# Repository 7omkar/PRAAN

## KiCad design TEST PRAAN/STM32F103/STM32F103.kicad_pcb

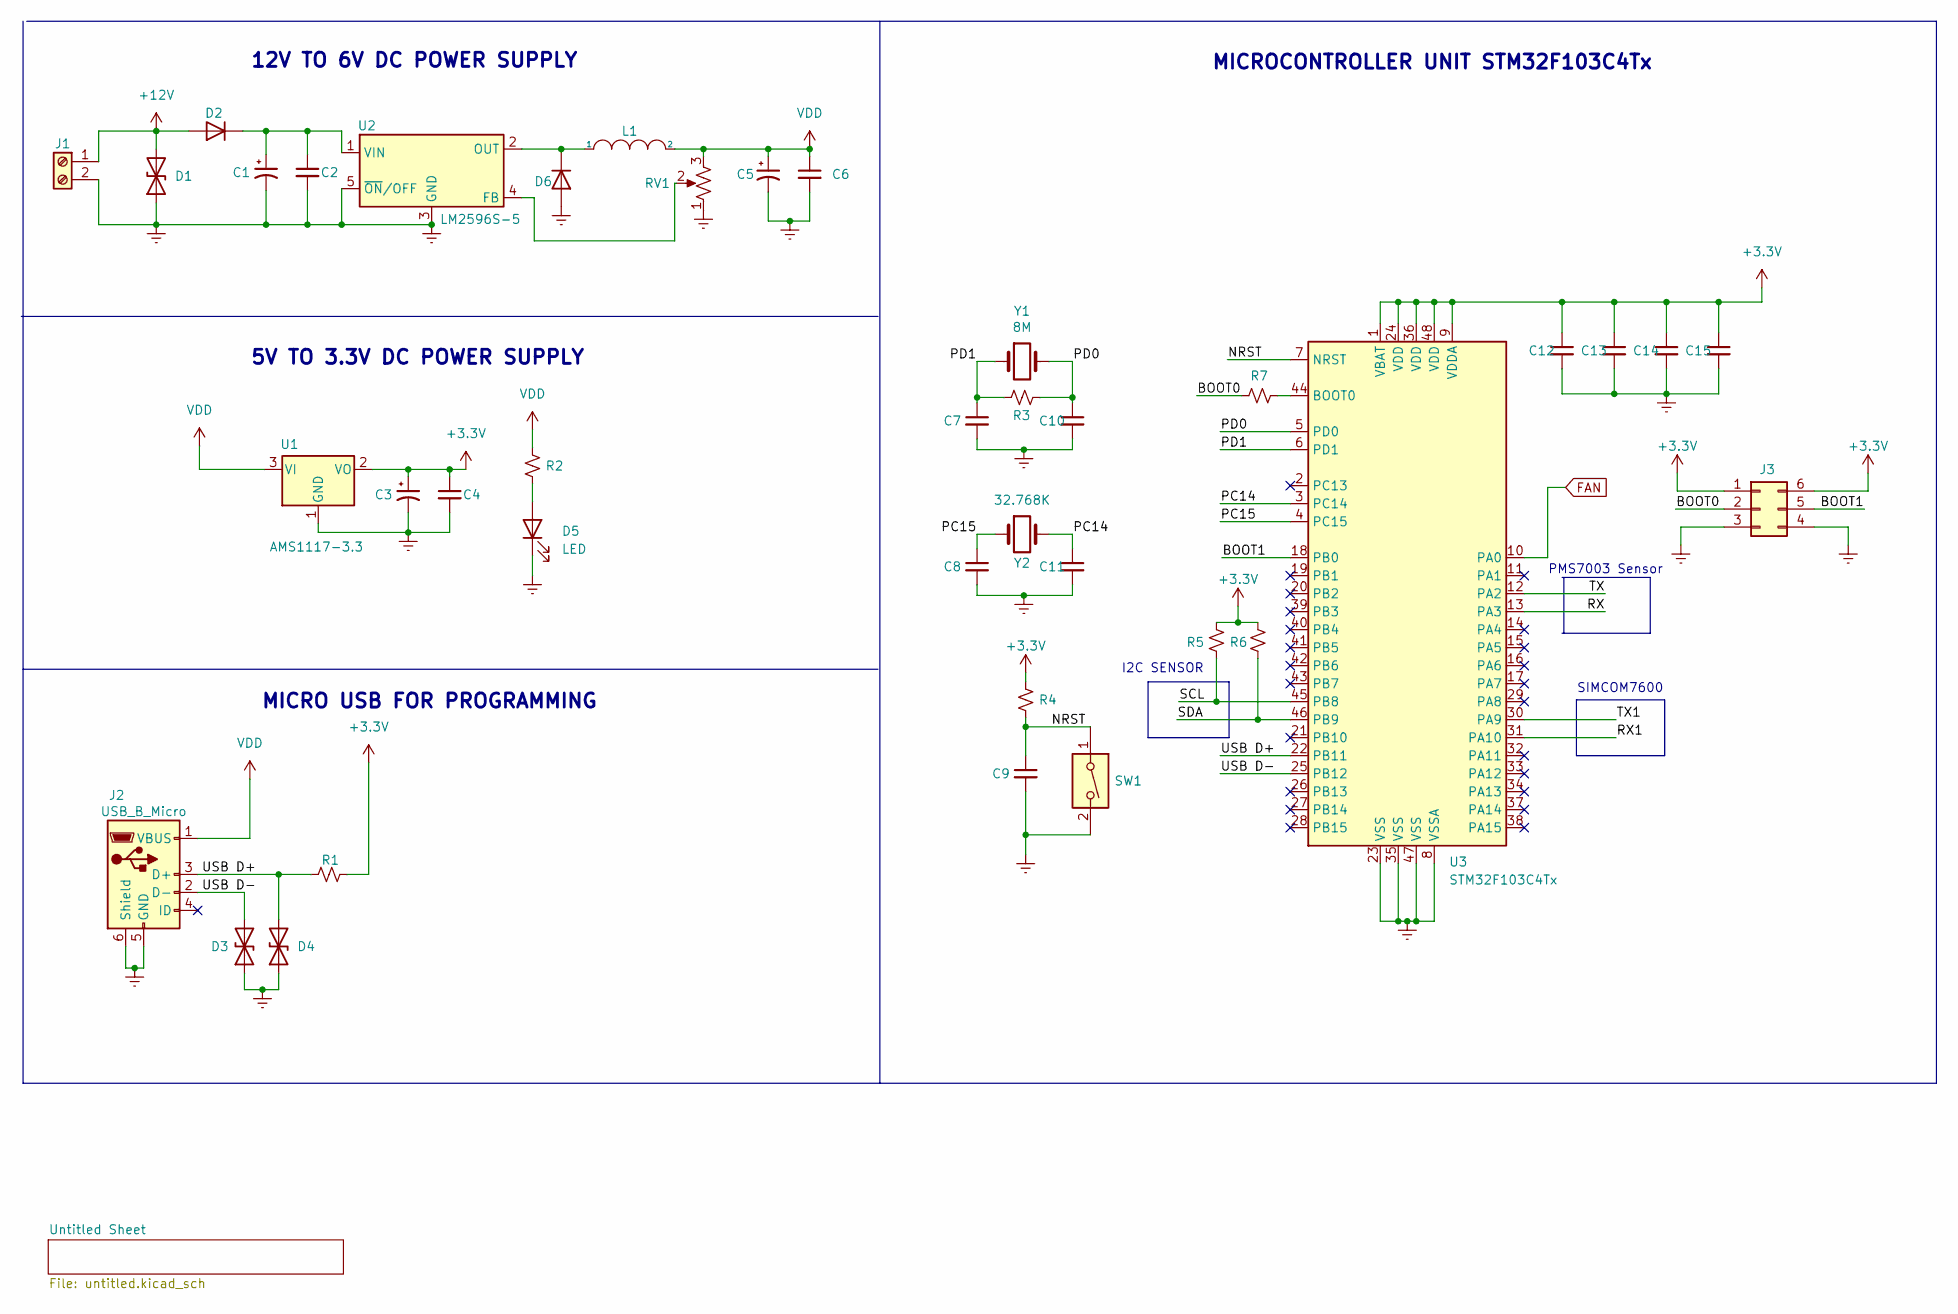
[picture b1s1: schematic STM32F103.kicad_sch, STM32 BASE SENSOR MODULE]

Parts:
C1, C3, C5: 470uf 25V; CP_Elec_5x5.8
C2, C4, C6, C12, C14: 0.1uf 50V; C_0805_2012Metric_Pad1.18x1.45mm_HandSolder
C7, C8, C9, C10, C11: 22pf 50V; C_0805_2012Metric_Pad1.18x1.45mm_HandSolder
C13, C15: 10uf 50V; C_0805_2012Metric_Pad1.18x1.45mm_HandSolder
D1, D3, D4: D_TVS; D_SOD-123
D2, D6: SS34; D_SMA
D5: LED; LED_0805_2012Metric_Pad1.15x1.40mm_HandSolder
J1: Screw_Terminal_01x02; TerminalBlock_Phoenix_MKDS-3-2-5.08_1x02_P5.08mm_Horizontal
J2: USB_B_Micro; USB_Micro-B_Molex-105017-0001
J3: Conn_02x03_Counter_Clockwise; PinHeader_2x03_P2.54mm_Vertical
L1: INDUCTOR; L_2512_6332Metric_Pad1.52x3.35mm_HandSolder
R1: 1.5K; R_0805_2012Metric_Pad1.20x1.40mm_HandSolder
R2, R4, R5, R6: 1K; R_0805_2012Metric_Pad1.20x1.40mm_HandSolder
R3: 10M; R_0805_2012Metric_Pad1.20x1.40mm_HandSolder
R7: 10K; R_0805_2012Metric_Pad1.20x1.40mm_HandSolder
RV1: 10K; Potentiometer_Bourns_3266W_Vertical
SW1: SW_DIP_x01; SW_PUSH_6mm_H5mm
U1: AMS1117-3.3; SOT-223-3_TabPin2
U2: LM2596S-5; TO-263-5_TabPin3
U3: STM32F103C4Tx; LQFP-48_7x7mm_P0.5mm
Y1: 8M; Crystal_HC18-U_Vertical
Y2: 32.768K; Crystal_HC18-U_Vertical

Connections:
+3V3: C3.1, C4.1, C12.1, C13.1, C14.1, C15.1, J3.1, J3.6, R1.2, R4.1, R5.1, R6.1, U1.2 (VO), U3.1 (VBAT), U3.9 (VDDA), U3.24 (VDD), U3.36 (VDD), U3.48 (VDD); also elsewhere on the board
+12V: D1.2 (A2), D2.1 (A), J1.1; also elsewhere on the board
/BOOT0: J3.2, R7.1
/BOOT1: J3.5, U3.18 (PB0)
/NRST: C9.1, R4.2, SW1.1, U3.7 (NRST)
/PC14: C11.1, U3.3 (PC14), Y2.2
/PC15: C8.1, U3.4 (PC15), Y2.1
/PD0: C10.1, R3.2, U3.5 (PD0), Y1.2
/PD1: C7.1, R3.1, U3.6 (PD1), Y1.1
/RX: U3.13 (PA3)
/RX1: U3.31 (PA10)
/SCL: R5.2, U3.45 (PB8)
/SDA: R6.2, U3.46 (PB9)
/TX: U3.12 (PA2)
/TX1: U3.30 (PA9)
/USB D+: D4.2 (A2), J2.3 (D+), R1.1, U3.22 (PB11)
/USB D-: D3.2 (A2), J2.2 (D-), U3.25 (PB12)
Earth: C1.2, C2.2, C3.2, C4.2, C5.2, C6.2, C7.2, C8.2, C9.2, C10.2, C11.2, C12.2, C13.2, C14.2, C15.2, D1.1 (A1), D3.1 (A1), D4.1 (A1), D5.1 (K), D6.1 (A), J1.2, J2.5 (GND), J2.6 (Shield), J3.3, J3.4, RV1.1, SW1.2, U1.1 (GND), U2.3 (GND), U2.5 (~ON/OFF), U3.8 (VSSA), U3.23 (VSS), U3.35 (VSS), U3.47 (VSS); also elsewhere on the board
FAN: U3.10 (PA0); also elsewhere on the board
unnamed: C1.1, C2.1, D2.2 (K), U2.1 (VIN)
unnamed: D5.2 (A), R2.2
unnamed: D6.2 (K), L1.1, U2.2 (OUT)
unnamed: R7.2, U3.44 (BOOT0)
unnamed: RV1.2, U2.4 (FB)
VDD: C5.1, C6.1, J2.1 (VBUS), L1.2, R2.1, RV1.3, U1.3 (VI); also elsewhere on the board

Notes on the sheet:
I2C SENSOR
SIMCOM7600
12V TO 6V DC POWER SUPPLY
PMS7003 Sensor
MICRO USB FOR PROGRAMMING
5V TO 3.3V DC POWER SUPPLY
MICROCONTROLLER UNIT STM32F103C4Tx

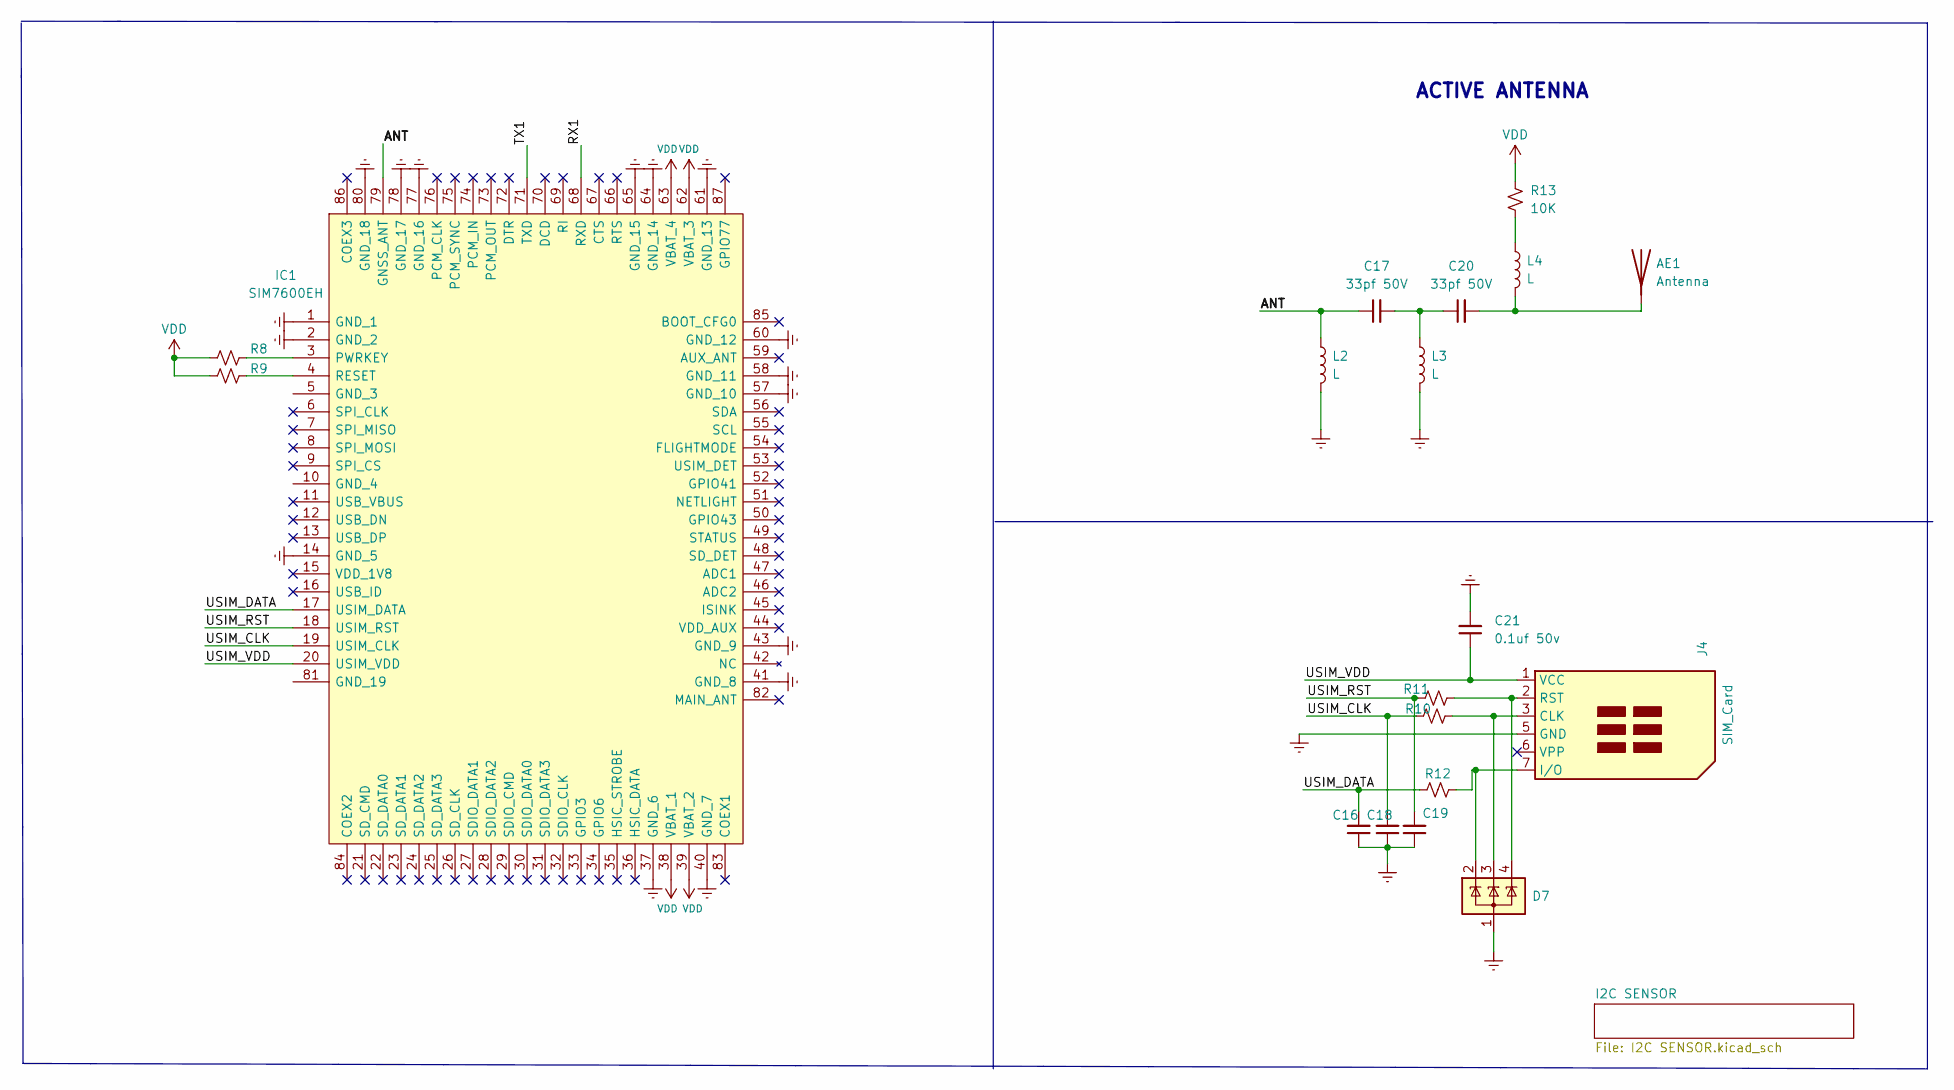
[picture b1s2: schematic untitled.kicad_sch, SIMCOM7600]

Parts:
AE1: Antenna; Texas_SWRA117D_2.4GHz_Right
C16, C18, C19: 22pf 50v; C_0805_2012Metric_Pad1.18x1.45mm_HandSolder
C17, C20: 33pf 50V; C_0805_2012Metric_Pad1.18x1.45mm_HandSolder
C21: 0.1uf 50v; C_0805_2012Metric_Pad1.18x1.45mm_HandSolder
D7: SP0503BAHT; SOT-143
IC1: SIM7600EH; Manufacturer_Part_Number SIM7600EH
J4: SIM_Card; microSIM_JAE_SF53S006VCBR2000
L2, L3, L4: L; L_1206_3216Metric_Pad1.42x1.75mm_HandSolder
R8, R9, R13: 10K; R_0805_2012Metric_Pad1.20x1.40mm_HandSolder
R10, R11, R12: 22R; R_0805_2012Metric_Pad1.20x1.40mm_HandSolder

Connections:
/Untitled Sheet/ANT: C17.1, IC1.79 (GNSS_ANT), L2.1
/Untitled Sheet/RX1: IC1.68 (RXD)
/Untitled Sheet/TX1: IC1.71 (TXD)
/Untitled Sheet/USIM_CLK: C18.2, IC1.19 (USIM_CLK), R10.1
/Untitled Sheet/USIM_DATA: C16.2, IC1.17 (USIM_DATA), R12.1
/Untitled Sheet/USIM_RST: C19.2, IC1.18 (USIM_RST), R11.1
/Untitled Sheet/USIM_VDD: C21.1, IC1.20 (USIM_VDD), J4.1 (VCC)
Earth: C16.1, C18.1, C19.1, C21.2, D7.1 (A), IC1.1 (GND_1), IC1.2 (GND_2), IC1.14 (GND_5), IC1.37 (GND_6), IC1.40 (GND_7), IC1.41 (GND_8), IC1.43 (GND_9), IC1.57 (GND_10), IC1.58 (GND_11), IC1.60 (GND_12), IC1.61 (GND_13), IC1.64 (GND_14), IC1.65 (GND_15), IC1.77 (GND_16), IC1.78 (GND_17), IC1.80 (GND_18), J4.5 (GND), L2.2, L3.2; also elsewhere on the board
unnamed: AE1.1 (A), C20.2, L4.2
unnamed: C17.2, C20.1, L3.1
unnamed: D7.2 (K), J4.7 (I/O), R12.2
unnamed: D7.3 (K), J4.3 (CLK), R10.2
unnamed: D7.4 (K), J4.2 (RST), R11.2
unnamed: IC1.3 (PWRKEY), R8.2
unnamed: IC1.4 (RESET), R9.2
unnamed: L4.1, R13.2
VDD: IC1.38 (VBAT_1), IC1.39 (VBAT_2), IC1.62 (VBAT_3), IC1.63 (VBAT_4), R8.1, R9.1, R13.1; also elsewhere on the board

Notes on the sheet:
ACTIVE ANTENNA

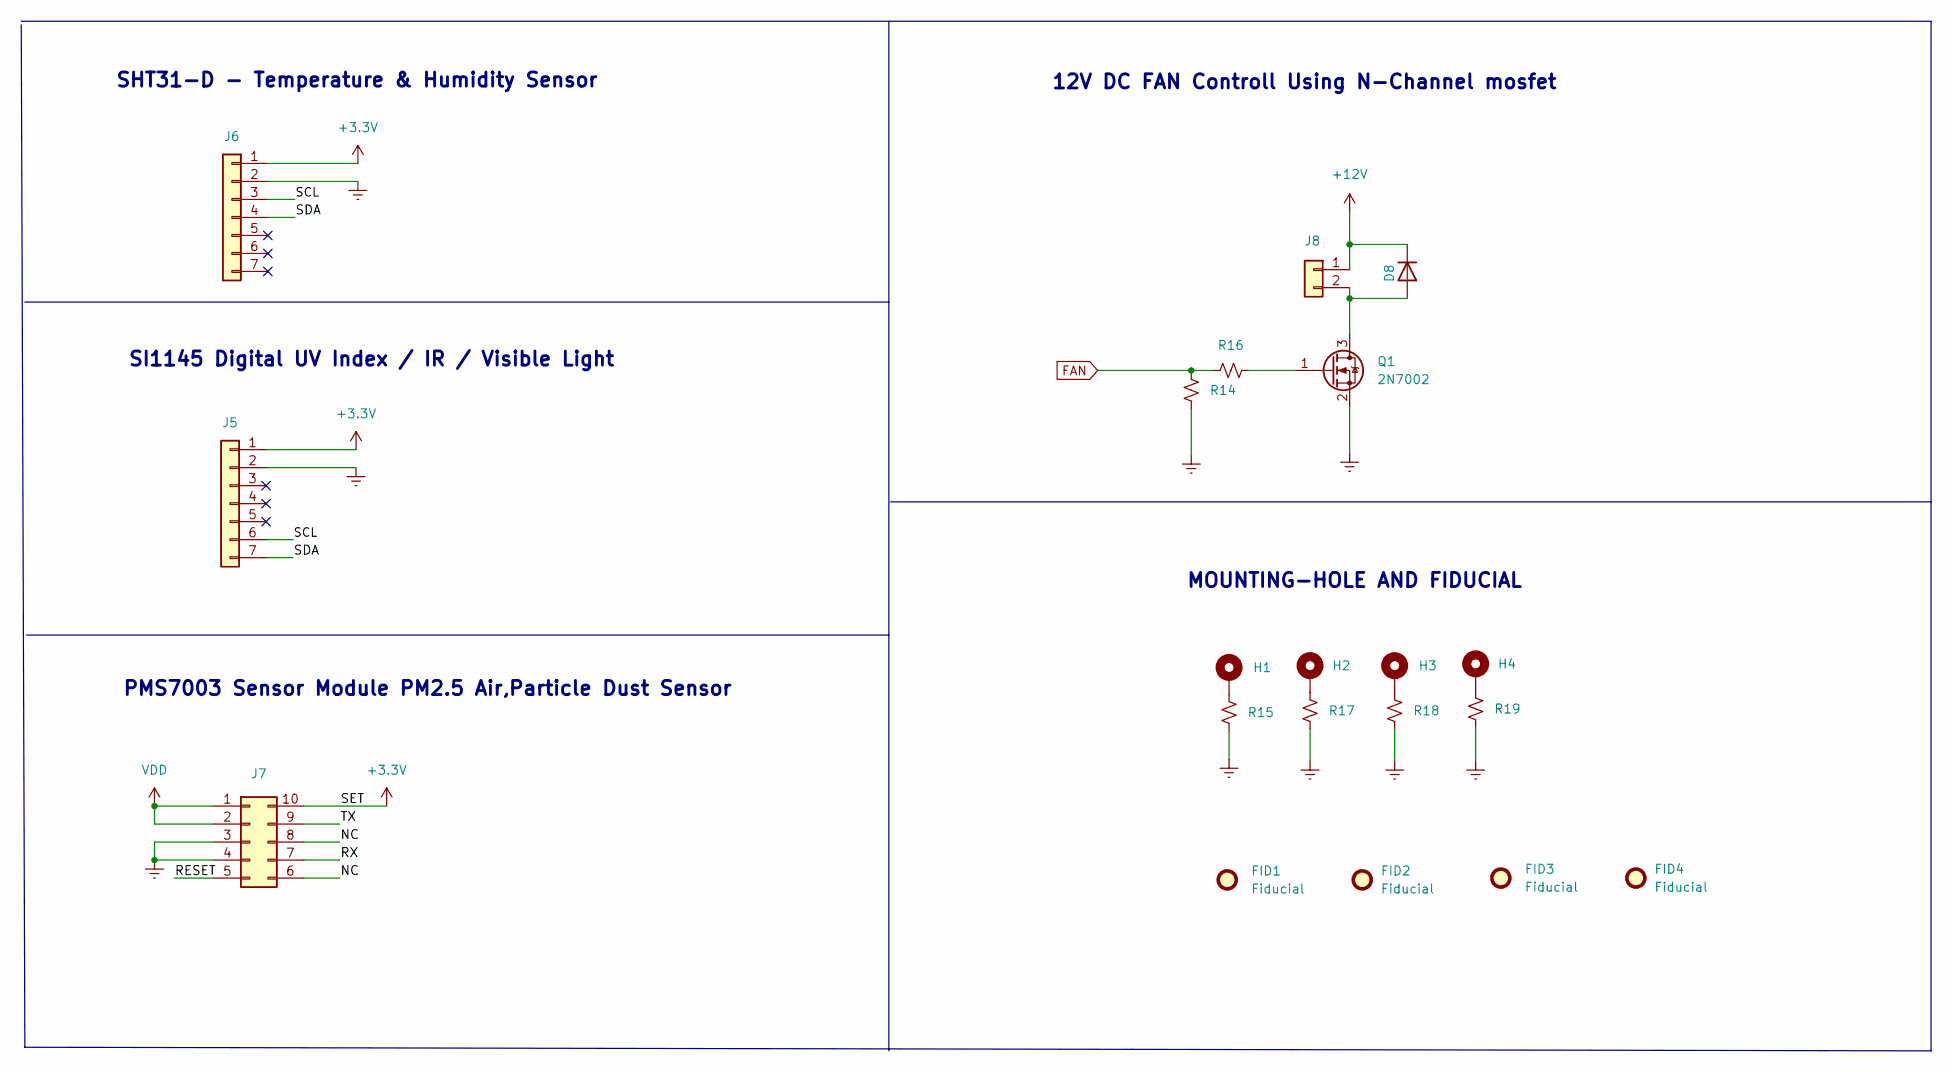
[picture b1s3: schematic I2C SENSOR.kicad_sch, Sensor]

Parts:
D8: SS34; D_SMA
FID1, FID2, FID3, FID4: Fiducial; Fiducial_0.5mm_Mask1.5mm
H1, H2, H3, H4: MountingHole_Pad; MountingHole_2.7mm_M2.5_Pad_Via
J5, J6: Conn_01x07; PinHeader_1x07_P2.54mm_Vertical
J7: Conn_02x05_Counter_Clockwise; PinHeader_2x05_P2.54mm_Vertical
J8: Conn_01x02; JST_XA_B02B-XASK-1_1x02_P2.50mm_Vertical
Q1: 2N7002; SOT-23
R14, R15, R16, R17, R18, R19: 150R; R_0805_2012Metric_Pad1.20x1.40mm_HandSolder

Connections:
+3V3: J5.1, J6.1, J7.10; also elsewhere on the board
+12V: D8.2 (K), J8.1; also elsewhere on the board
/Untitled Sheet/I2C SENSOR/NC: J7.6, J7.8
/Untitled Sheet/I2C SENSOR/RESET: J7.5
/Untitled Sheet/I2C SENSOR/RX: J7.7
/Untitled Sheet/I2C SENSOR/SCL: J5.6, J6.3
/Untitled Sheet/I2C SENSOR/SDA: J5.7, J6.4
/Untitled Sheet/I2C SENSOR/TX: J7.9
Earth: J5.2, J6.2, J7.3, J7.4, Q1.2 (S), R14.1, R15.1, R17.1, R18.1, R19.1; also elsewhere on the board
FAN: R14.2, R16.1; also elsewhere on the board
unnamed: D8.1 (A), J8.2, Q1.3 (D)
unnamed: H1.1, R15.2
unnamed: H2.1, R17.2
unnamed: H3.1, R18.2
unnamed: H4.1, R19.2
unnamed: Q1.1 (G), R16.2
VDD: J7.1, J7.2; also elsewhere on the board

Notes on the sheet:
PMS7003 Sensor Module PM2.5 Air,Particle Dust Sensor
SHT31-D - Temperature & Humidity Sensor
MOUNTING-HOLE AND FIDUCIAL
SI1145 Digital UV Index / IR / Visible Light
12V DC FAN Controll Using N-Channel mosfet

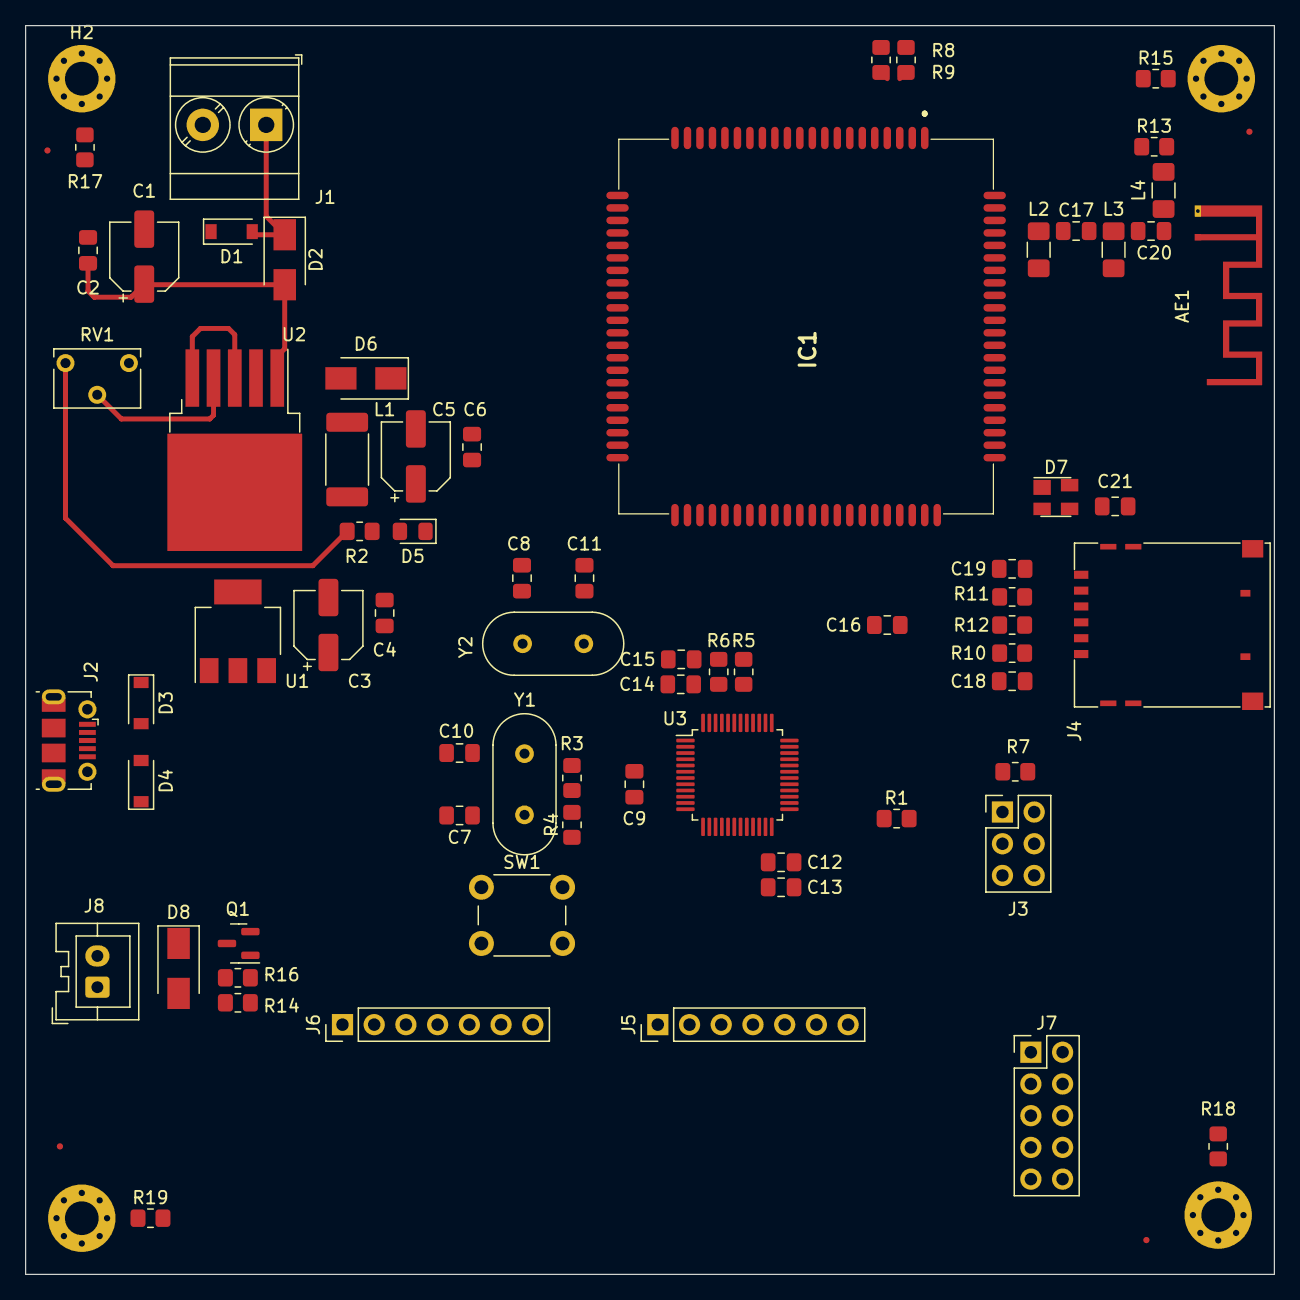
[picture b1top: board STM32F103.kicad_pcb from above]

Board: 2 copper layers, 100.0 x 100.0 mm, 78 parts (0 on the bottom side), 43 nets.
